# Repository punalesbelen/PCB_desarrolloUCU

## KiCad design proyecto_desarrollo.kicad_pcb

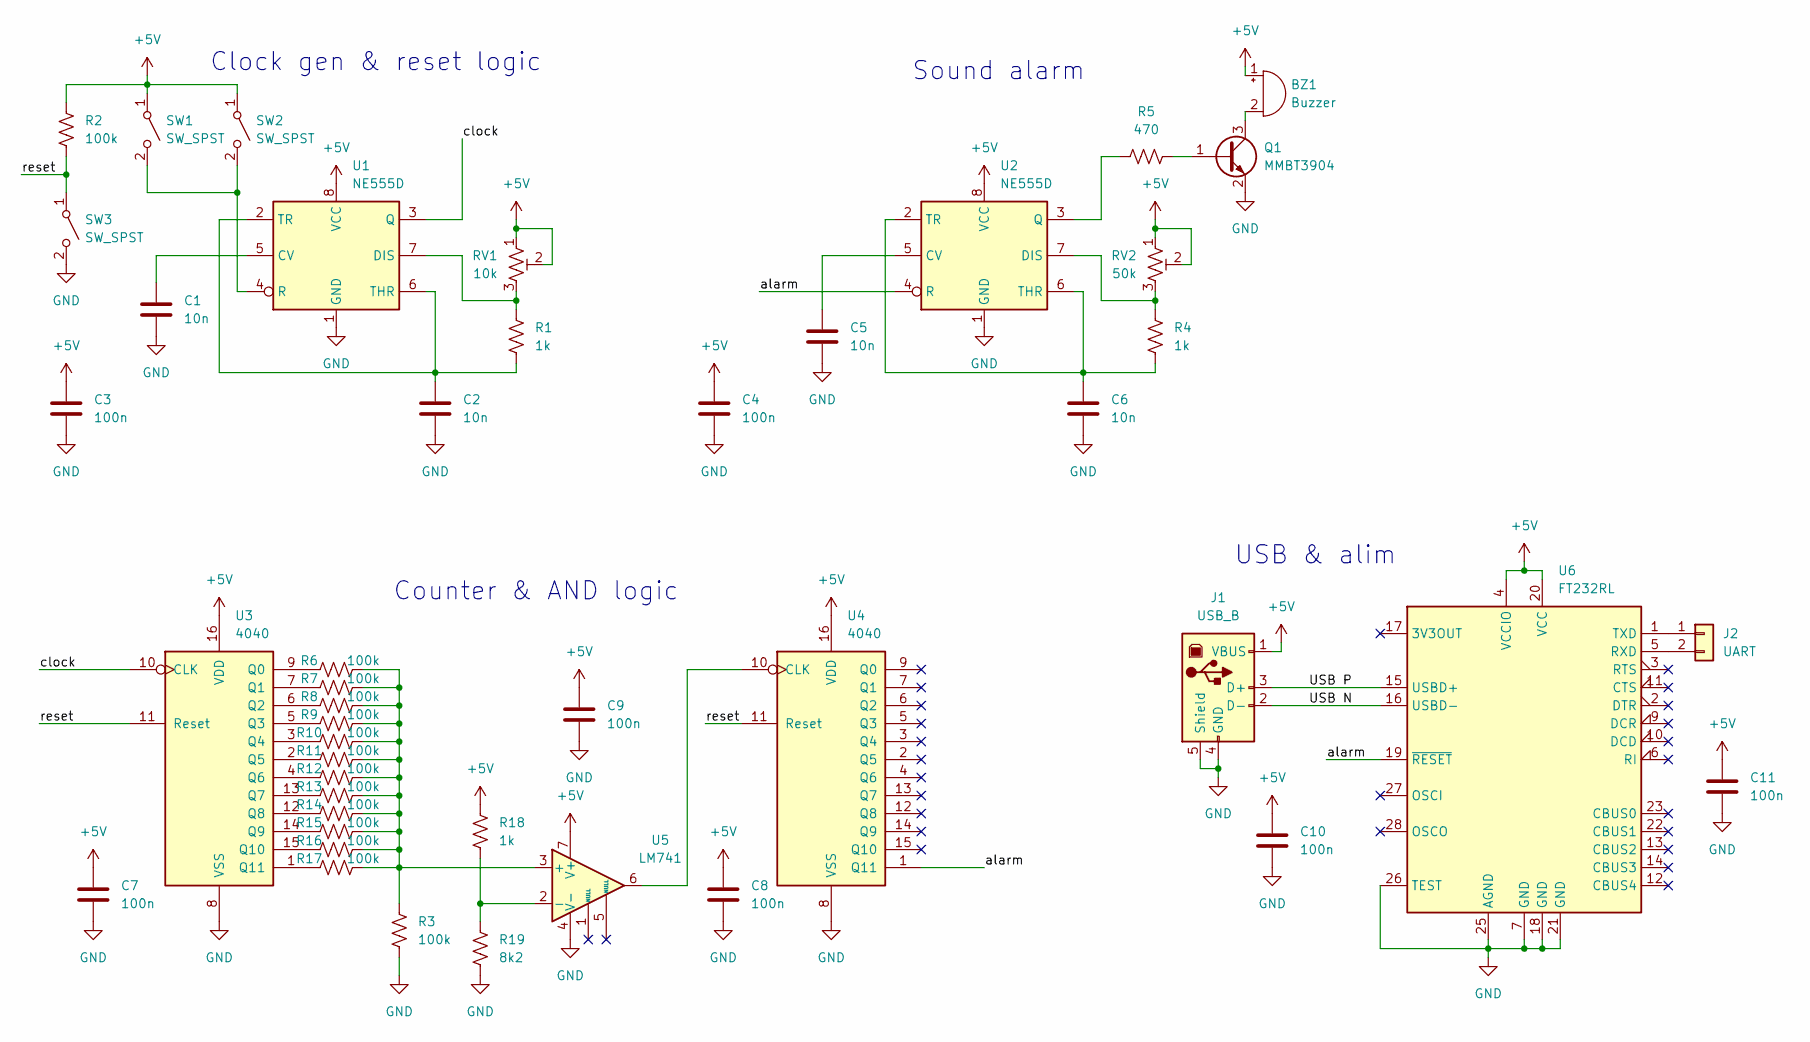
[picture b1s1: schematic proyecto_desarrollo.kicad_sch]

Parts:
BZ1: Buzzer; MagneticBuzzer_PUI_AT-0927-TT-6-R
C1, C2, C5, C6: 10n; C_0603_1608Metric
C3, C4, C7, C8, C9, C10, C11: 100n; C_0603_1608Metric
J1: USB_B; USB_Mini-B_Wuerth_65100516121_Horizontal
J2: UART; PinHeader_1x02_P2.54mm_Vertical
Q1: MMBT3904; SOT-23
R1, R4, R18: 1k; R_0603_1608Metric
R2, R3, R6, R7, R8, R9, R10, R11, R12, R13, R14, R15, R16, R17: 100k; R_0603_1608Metric
R5: 470; R_0603_1608Metric
R19: 8k2; R_0603_1608Metric
RV1: 10k; 601030_AVX
RV2: 50k; 601030_AVX
SW1, SW2, SW3: SW_SPST; SW_PUSH_6mm_H9.5mm
U1, U2: NE555D; SOIC-8_3.9x4.9mm_P1.27mm
U3, U4: 4040; SO-16_3.9x9.9mm_P1.27mm
U5: LM741; SOIC-8_3.9x4.9mm_P1.27mm
U6: FT232RL; SSOP-28_5.3x10.2mm_P0.65mm

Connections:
+5V: BZ1.1 (+), C3.1, C4.1, C7.1, C8.1, C9.1, C10.1, C11.1, J1.1 (VBUS), R2.1, R18.1, RV1.1, RV1.2, RV2.1, RV2.2, SW1.1 (A), SW2.1 (A), U1.8 (VCC), U2.8 (VCC), U3.16 (VDD), U4.16 (VDD), U5.7 (V+), U6.4 (VCCIO), U6.20 (VCC)
/USB N: J1.2 (D-), U6.16 (USBD-)
/USB P: J1.3 (D+), U6.15 (USBD+)
/alarm: U2.4 (R), U4.1 (Q11), U6.19 (~RESET)
/clock: U1.3 (Q), U3.10 (CLK)
/reset: R2.2, SW3.1 (A), U3.11 (Reset), U4.11 (Reset)
GND: C1.2, C2.2, C3.2, C4.2, C5.2, C6.2, C7.2, C8.2, C9.2, C10.2, C11.2, J1.4 (GND), J1.5 (Shield), Q1.2 (E), R3.2, R19.2, SW3.2 (B), U1.1 (GND), U2.1 (GND), U3.8 (VSS), U4.8 (VSS), U5.4 (V-), U6.7 (GND), U6.18 (GND), U6.21 (GND), U6.25 (AGND), U6.26 (TEST)
unnamed: BZ1.2 (-), Q1.3 (C)
unnamed: J2.1, U6.1 (TXD)
unnamed: J2.2, U6.5 (RXD)
unnamed: Q1.1 (B), R5.2
unnamed: SW1.2 (B), SW2.2 (B), U1.4 (R)
unnamed: C1.1, U1.5 (CV)
unnamed: R1.1, RV1.3, U1.7 (DIS)
unnamed: C2.1, R1.2, U1.2 (TR), U1.6 (THR)
unnamed: C5.1, U2.5 (CV)
unnamed: R4.1, RV2.3, U2.7 (DIS)
unnamed: R5.1, U2.3 (Q)
unnamed: C6.1, R4.2, U2.2 (TR), U2.6 (THR)
unnamed: R6.1, U3.9 (Q0)
unnamed: R7.1, U3.7 (Q1)
unnamed: R8.1, U3.6 (Q2)
unnamed: R9.1, U3.5 (Q3)
unnamed: R10.1, U3.3 (Q4)
unnamed: R11.1, U3.2 (Q5)
unnamed: R12.1, U3.4 (Q6)
unnamed: R13.1, U3.13 (Q7)
unnamed: R14.1, U3.12 (Q8)
unnamed: R15.1, U3.14 (Q9)
unnamed: R16.1, U3.15 (Q10)
unnamed: R17.1, U3.1 (Q11)
unnamed: U4.10 (CLK), U5.6
unnamed: R3.1, R6.2, R7.2, R8.2, R9.2, R10.2, R11.2, R12.2, R13.2, R14.2, R15.2, R16.2, R17.2, U5.3 (+)
unnamed: R18.2, R19.1, U5.2 (-)

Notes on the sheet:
Counter & AND logic
Sound alarm
USB & alim
Clock gen & reset logic

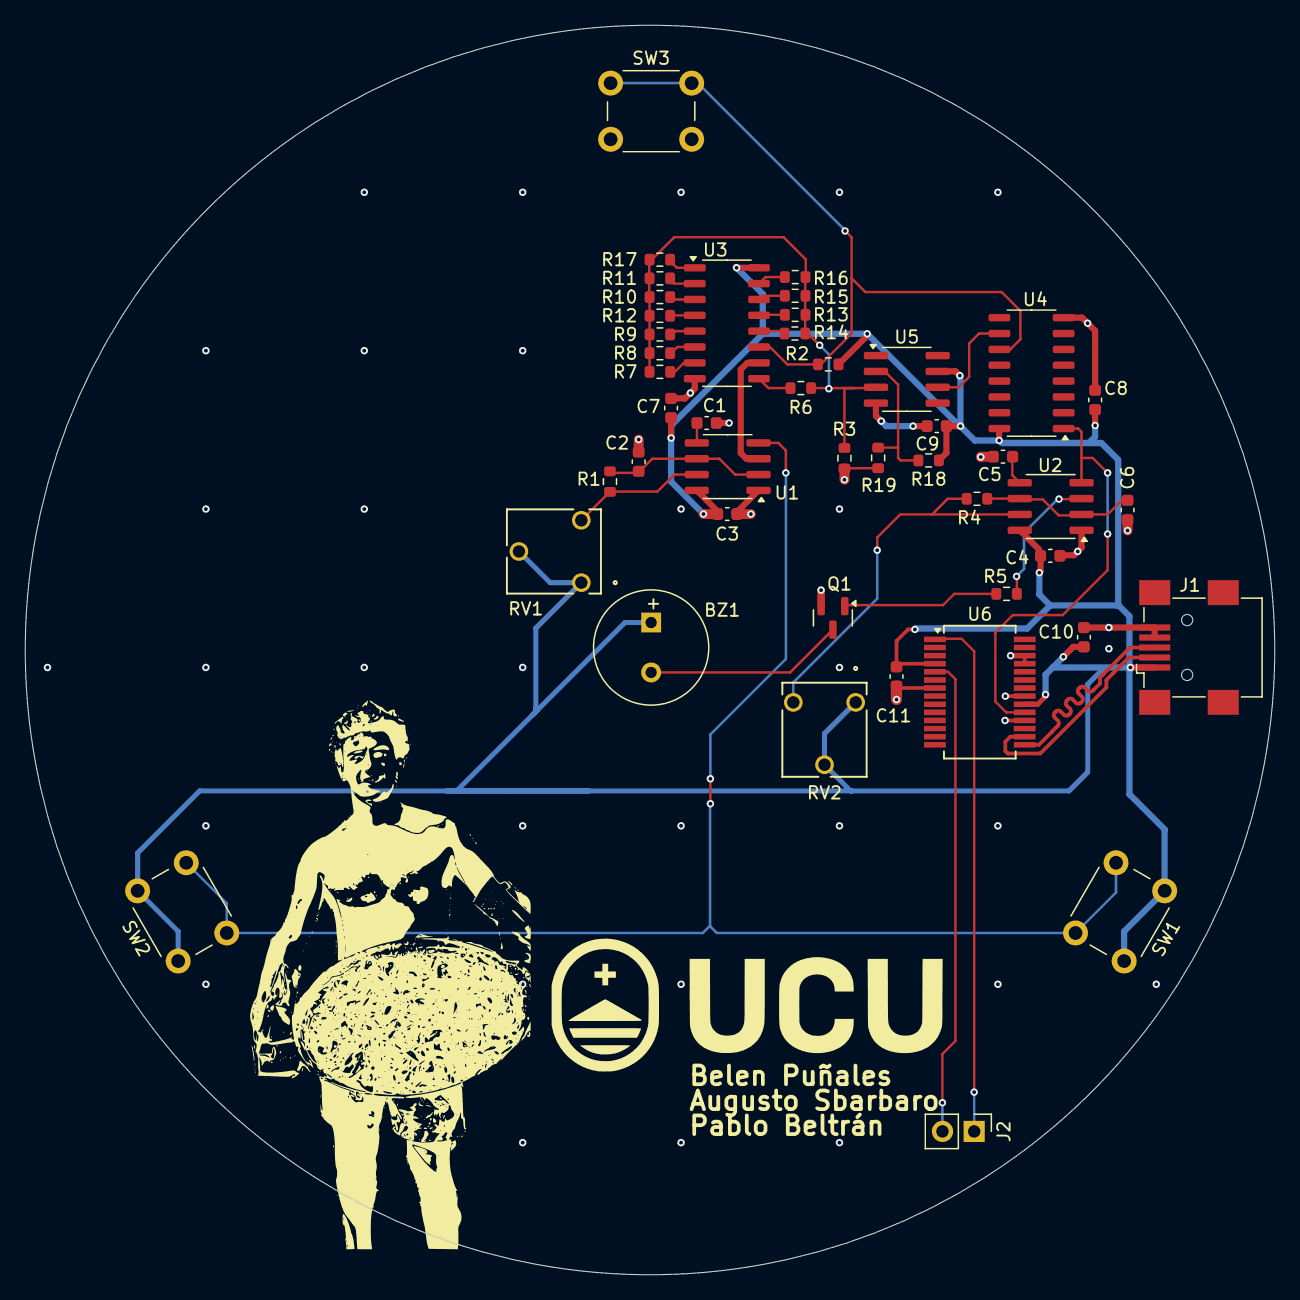
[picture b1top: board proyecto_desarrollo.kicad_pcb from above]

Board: 4 copper layers, 100.2 x 100.2 mm, 45 parts (0 on the bottom side), 34 nets.
